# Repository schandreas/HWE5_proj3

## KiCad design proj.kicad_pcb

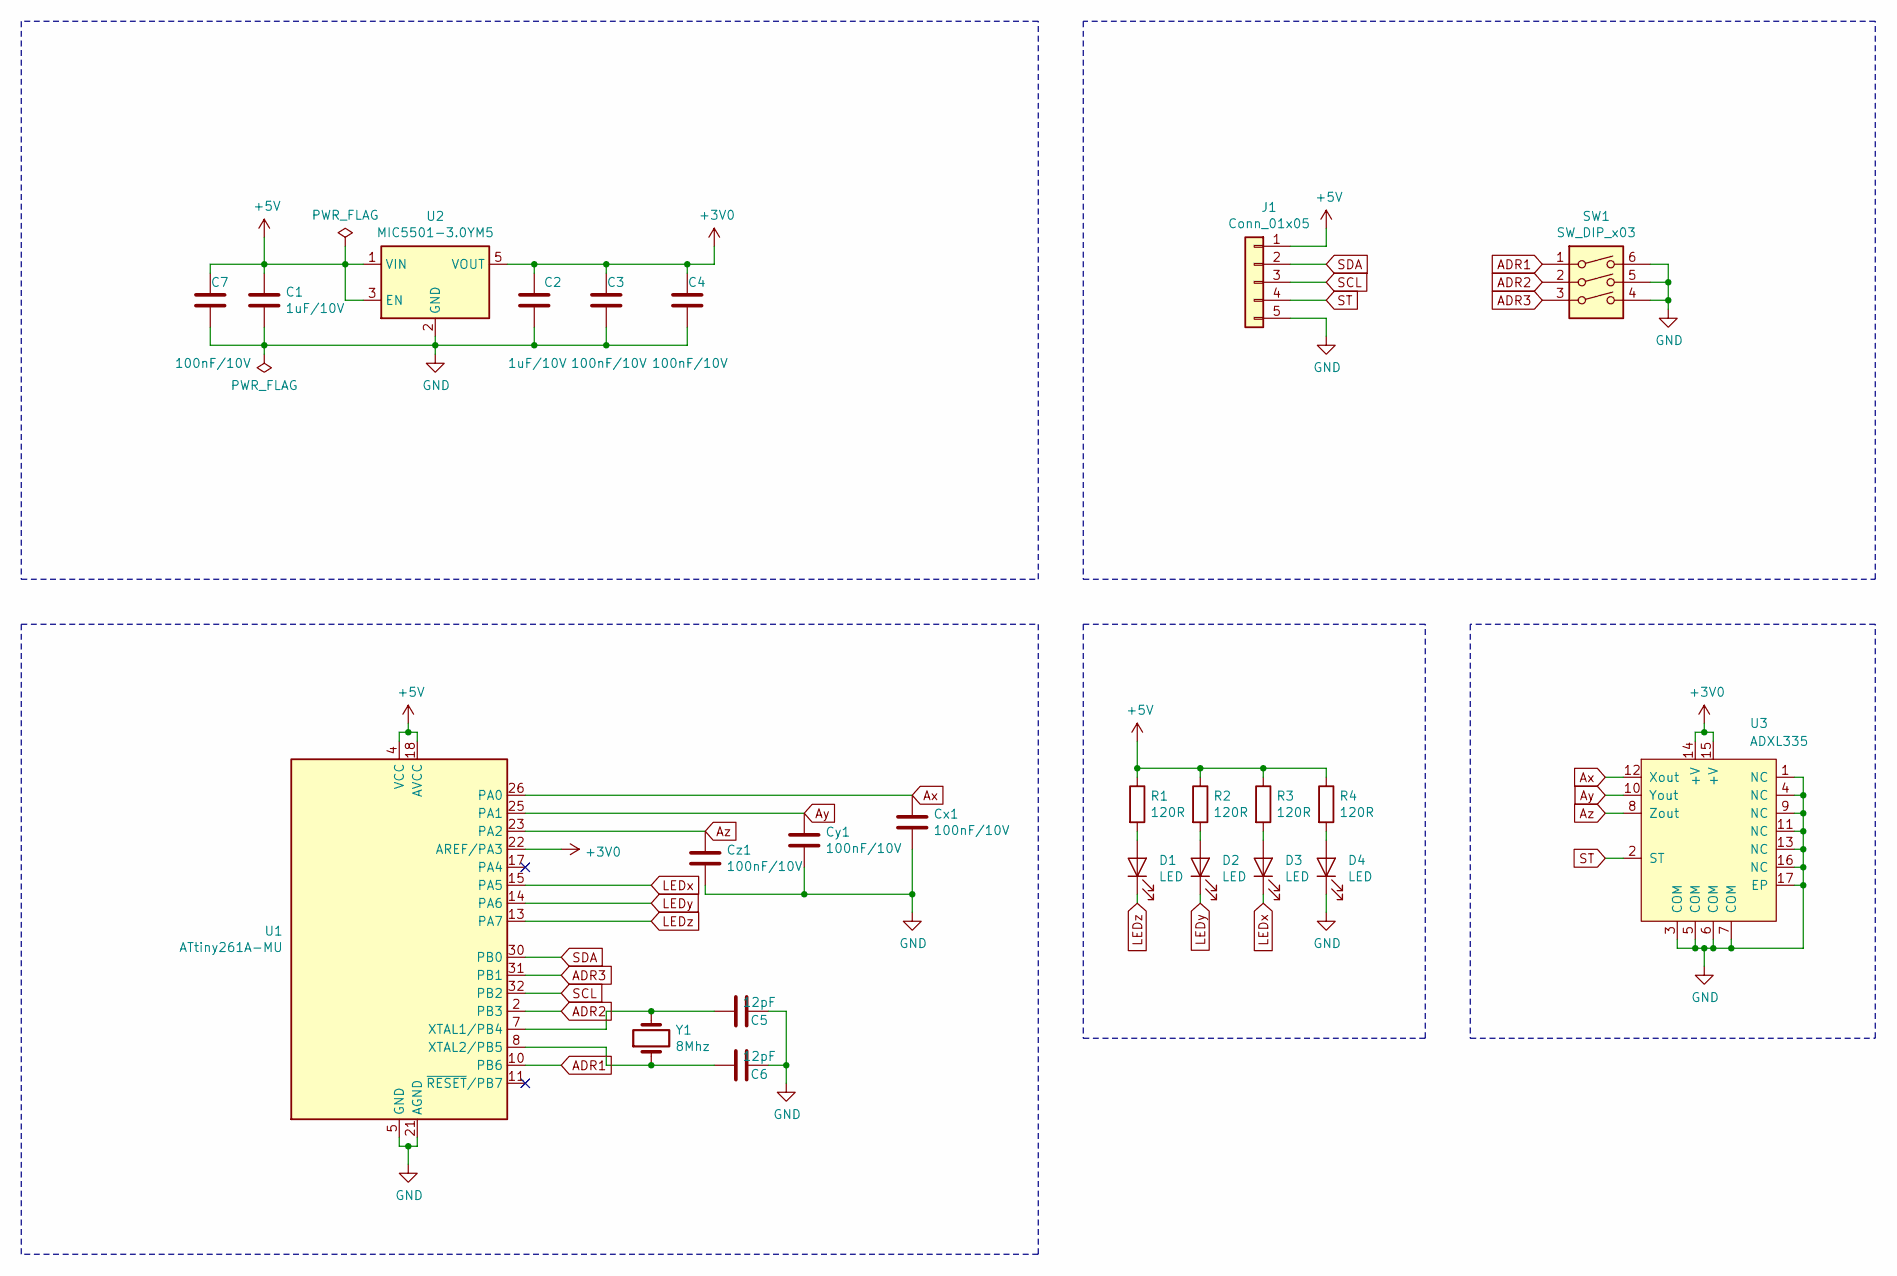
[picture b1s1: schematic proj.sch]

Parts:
C1, C2: 1uF/10V; C_0603_1608Metric
C3, C4, C7: 100nF/10V; C_0201_0603Metric
C5, C6: 12pF; C_0201_0603Metric
Cx1: 100nF/10V; C_0201_0603Metric
Cy1: 100nF/10V; C_0201_0603Metric
Cz1: 100nF/10V; C_0201_0603Metric
D1, D2, D3, D4: LED; LED_0603_1608Metric_Castellated
J1: Conn_01x05; PinHeader_1x05_P2.54mm_Horizontal
R1, R2, R3, R4: 120R; R_0603_1608Metric
SW1: SW_DIP_x03; SW_DIP_SPSTx03_Slide_6.7x9.18mm_W7.62mm_P2.54mm_LowProfile
U1: ATtiny261A-MU; QFN-32-1EP_5x5mm_P0.5mm_EP3.1x3.1mm
U2: MIC5501-3.0YM5; SOT-23-5
U3: ADXL335; QFN-16-1EP_4x4mm_P0.65mm_EP2.1x2.1mm
Y1: 8Mhz; Crystal_SMD_HC49-SD

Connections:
+3V0: C2.1, C3.1, C4.1, U1.22 (AREF/PA3), U2.5 (VOUT), U3.14 (+V), U3.15 (+V)
+5V: C1.1, C7.1, J1.1, R1.1, R2.1, R3.1, R4.1, U1.4 (VCC), U1.18 (AVCC), U2.1 (VIN), U2.3 (EN)
ADR1: SW1.1, U1.10 (PB6)
ADR2: SW1.2, U1.2 (PB3)
ADR3: SW1.3, U1.31 (PB1)
Ax: Cx1.1, U1.26 (PA0), U3.12 (Xout)
Ay: Cy1.1, U1.25 (PA1), U3.10 (Yout)
Az: Cz1.1, U1.23 (PA2), U3.8 (Zout)
GND: C1.2, C2.2, C3.2, C4.2, C5.2, C6.2, C7.2, Cx1.2, Cy1.2, Cz1.2, D4.1 (K), J1.5, SW1.4, SW1.5, SW1.6, U1.5 (GND), U1.21 (AGND), U1.33 (GND), U2.2 (GND), U3.1 (NC), U3.3 (COM), U3.4 (NC), U3.5 (COM), U3.6 (COM), U3.7 (COM), U3.9 (NC), U3.11 (NC), U3.13 (NC), U3.16 (NC), U3.17 (EP)
LEDx: D3.1 (K), U1.15 (PA5)
LEDy: D2.1 (K), U1.14 (PA6)
LEDz: D1.1 (K), U1.13 (PA7)
unnamed: C5.1, U1.7 (XTAL1/PB4), Y1.2
unnamed: C6.1, U1.8 (XTAL2/PB5), Y1.1
unnamed: D1.2 (A), R1.2
unnamed: D2.2 (A), R2.2
unnamed: D3.2 (A), R3.2
unnamed: D4.2 (A), R4.2
SCL: J1.3, U1.32 (PB2)
SDA: J1.2, U1.30 (PB0)
ST: J1.4, U3.2 (ST)

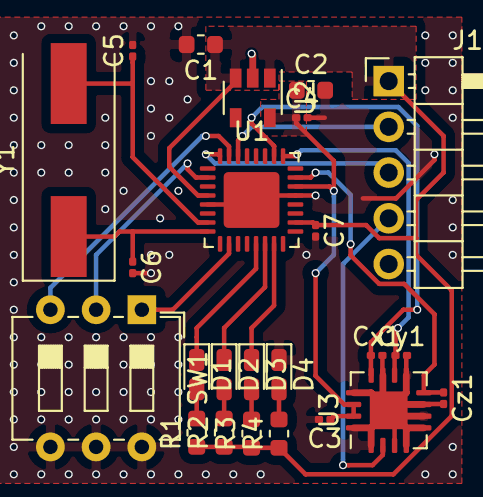
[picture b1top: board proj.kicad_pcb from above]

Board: 2 copper layers, 24 parts (0 on the bottom side), 21 nets.

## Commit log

2020-02-06 quieres? bro?
